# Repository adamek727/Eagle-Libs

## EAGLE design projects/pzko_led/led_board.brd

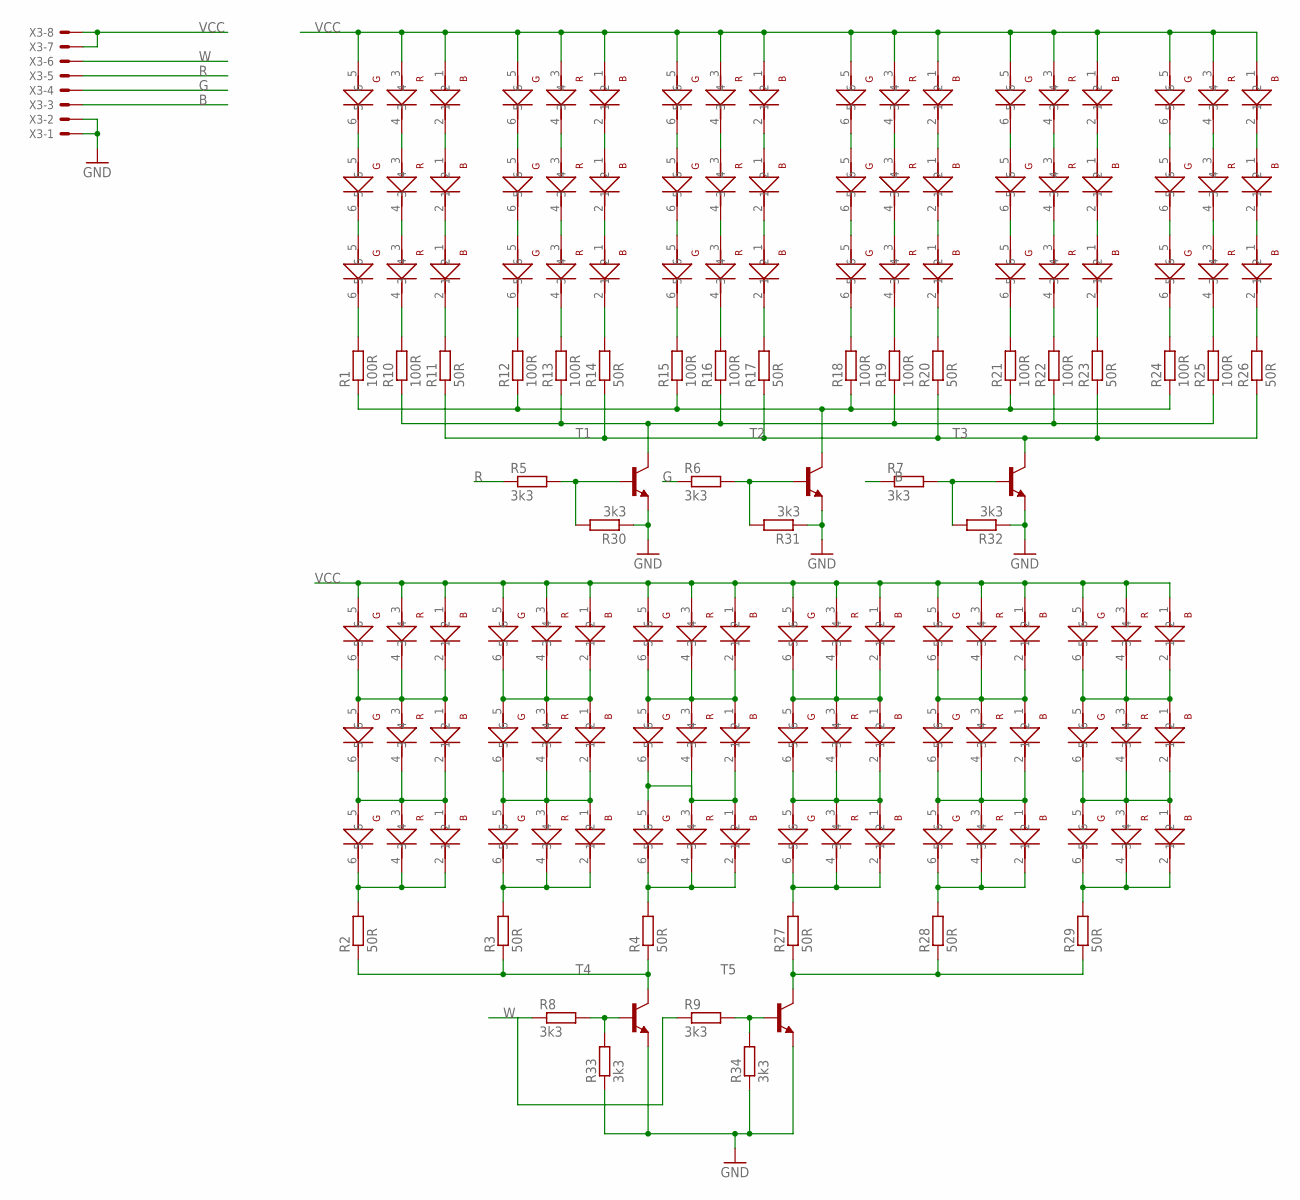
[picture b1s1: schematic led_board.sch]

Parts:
R1, R10, R12, R13, R15, R16, R18, R19, R21, R22, R24, R25: 100R; M1206
R2, R3, R4, R11, R14, R17, R20, R23, R26, R27, R28, R29: 50R; M1206
R5, R6, R7, R8, R9, R30, R31, R32, R33, R34: 3k3; M1206
T1, T2, T3, T4, T5: -NPN-SOT223; SOT223
U$1, U$2, U$3, U$4, U$5, U$6, U$7, U$8, U$9, U$10, U$11, U$12, U$13, U$14, U$15, U$16, U$17, U$18, U$19, U$20, U$21, U$22, U$23, U$24, U$25, U$26, U$27, U$28, U$29, U$30, U$31, U$32, U$33, U$34, U$35, U$38: 5050_LED
X3: KK-156-8

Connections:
B: R7.1, X3.3
G: R6.1, X3.4
GND: R30.1, R31.1, R32.1, R33.1, R34.1, T1.3 (E), T2.3 (E), T3.3 (E), T4.3 (E), T5.3 (E), X3.1, X3.2
unnamed: R6.2, R31.2, T2.1 (B)
unnamed: R7.2, R32.2, T3.1 (B)
unnamed: R11.1, R14.1, R17.1, R20.1, R23.1, R26.1, T3.4 (C)
unnamed: U$34.2, U$38.1
unnamed: R1.1, R12.1, R15.1, R18.1, R21.1, R24.1, T2.4 (C)
unnamed: U$34.4, U$38.3
unnamed: R10.1, R13.1, R16.1, R19.1, R22.1, R25.1, T1.4 (C)
unnamed: U$34.6, U$38.5
unnamed: U$1.1, U$38.2
unnamed: R5.2, R30.2, T1.1 (B)
unnamed: R8.2, R33.2, T4.1 (B)
unnamed: R9.2, R34.2, T5.1 (B)
unnamed: U$1.3, U$38.4
unnamed: U$1.5, U$38.6
unnamed: U$2.2, U$3.1
unnamed: U$2.4, U$3.3
unnamed: U$2.6, U$3.5
unnamed: U$3.2, U$4.1
unnamed: U$3.4, U$4.3
unnamed: U$3.6, U$4.5
unnamed: U$5.2, U$6.1
unnamed: U$5.4, U$6.3
unnamed: U$5.6, U$6.5
unnamed: U$6.2, U$7.1
unnamed: U$6.4, U$7.3
unnamed: U$6.6, U$7.5
unnamed: U$8.2, U$9.1
unnamed: U$8.4, U$9.3
unnamed: U$8.6, U$9.5
unnamed: U$9.2, U$10.1
unnamed: U$9.4, U$10.3
unnamed: U$9.6, U$10.5
unnamed: U$11.2, U$12.1
unnamed: U$11.4, U$12.3
unnamed: U$11.6, U$12.5
unnamed: U$12.2, U$13.1
unnamed: U$12.4, U$13.3
unnamed: U$12.6, U$13.5
unnamed: U$14.2, U$15.1
unnamed: U$14.4, U$15.3
unnamed: U$14.6, U$15.5
unnamed: U$15.2, U$16.1
unnamed: U$15.4, U$16.3
unnamed: U$15.6, U$16.5
unnamed: R1.2, U$1.6
unnamed: R10.2, U$1.4
unnamed: R11.2, U$1.2
unnamed: R12.2, U$4.6
unnamed: R13.2, U$4.4
unnamed: R15.2, U$7.6
unnamed: R16.2, U$7.4
unnamed: R17.2, U$7.2
unnamed: R18.2, U$10.6
unnamed: R19.2, U$10.4
unnamed: R21.2, U$13.6
unnamed: R22.2, U$13.4
unnamed: R23.2, U$13.2
unnamed: R24.2, U$16.6
unnamed: R26.2, U$16.2
unnamed: R25.2, U$16.4
unnamed: R20.2, U$10.2
unnamed: R14.2, U$4.2
unnamed: U$17.2, U$17.4, U$17.6, U$23.1, U$23.3, U$23.5
unnamed: U$18.2, U$18.4, U$18.6, U$24.1, U$24.3, U$24.5
unnamed: U$19.2, U$19.4, U$19.6, U$25.1, U$25.3, U$25.5
unnamed: U$20.2, U$20.4, U$20.6, U$26.1, U$26.3, U$26.5
unnamed: U$21.2, U$21.4, U$21.6, U$27.1, U$27.3, U$27.5
unnamed: U$22.2, U$22.4, U$22.6, U$28.1, U$28.3, U$28.5
unnamed: U$23.2, U$23.4, U$23.6, U$29.1, U$29.3, U$29.5
unnamed: U$24.2, U$24.4, U$24.6, U$30.1, U$30.3, U$30.5
unnamed: U$25.2, U$25.4, U$25.6, U$31.1, U$31.3, U$31.5
unnamed: U$26.2, U$26.4, U$26.6, U$32.1, U$32.3, U$32.5
unnamed: U$27.2, U$27.4, U$27.6, U$33.1, U$33.3, U$33.5
unnamed: U$28.2, U$28.4, U$28.6, U$35.1, U$35.3, U$35.5
unnamed: R2.2, U$29.2, U$29.4, U$29.6
unnamed: R29.2, U$35.2, U$35.4, U$35.6
unnamed: R28.2, U$33.2, U$33.4, U$33.6
unnamed: R27.2, U$32.2, U$32.4, U$32.6
unnamed: R4.2, U$31.2, U$31.4, U$31.6
unnamed: R3.2, U$30.2, U$30.4, U$30.6
unnamed: R27.1, R28.1, R29.1, T5.4 (C)
unnamed: R2.1, R3.1, R4.1, T4.4 (C)
R: R5.1, X3.5
VCC: U$2.1, U$2.3, U$2.5, U$5.1, U$5.3, U$5.5, U$8.1, U$8.3, U$8.5, U$11.1, U$11.3, U$11.5, U$14.1, U$14.3, U$14.5, U$17.1, U$17.3, U$17.5, U$18.1, U$18.3, U$18.5, U$19.1, U$19.3, U$19.5, U$20.1, U$20.3, U$20.5, U$21.1, U$21.3, U$21.5, U$22.1, U$22.3, U$22.5, U$34.1, U$34.3, U$34.5, X3.7, X3.8
W: R8.1, R9.1, X3.6

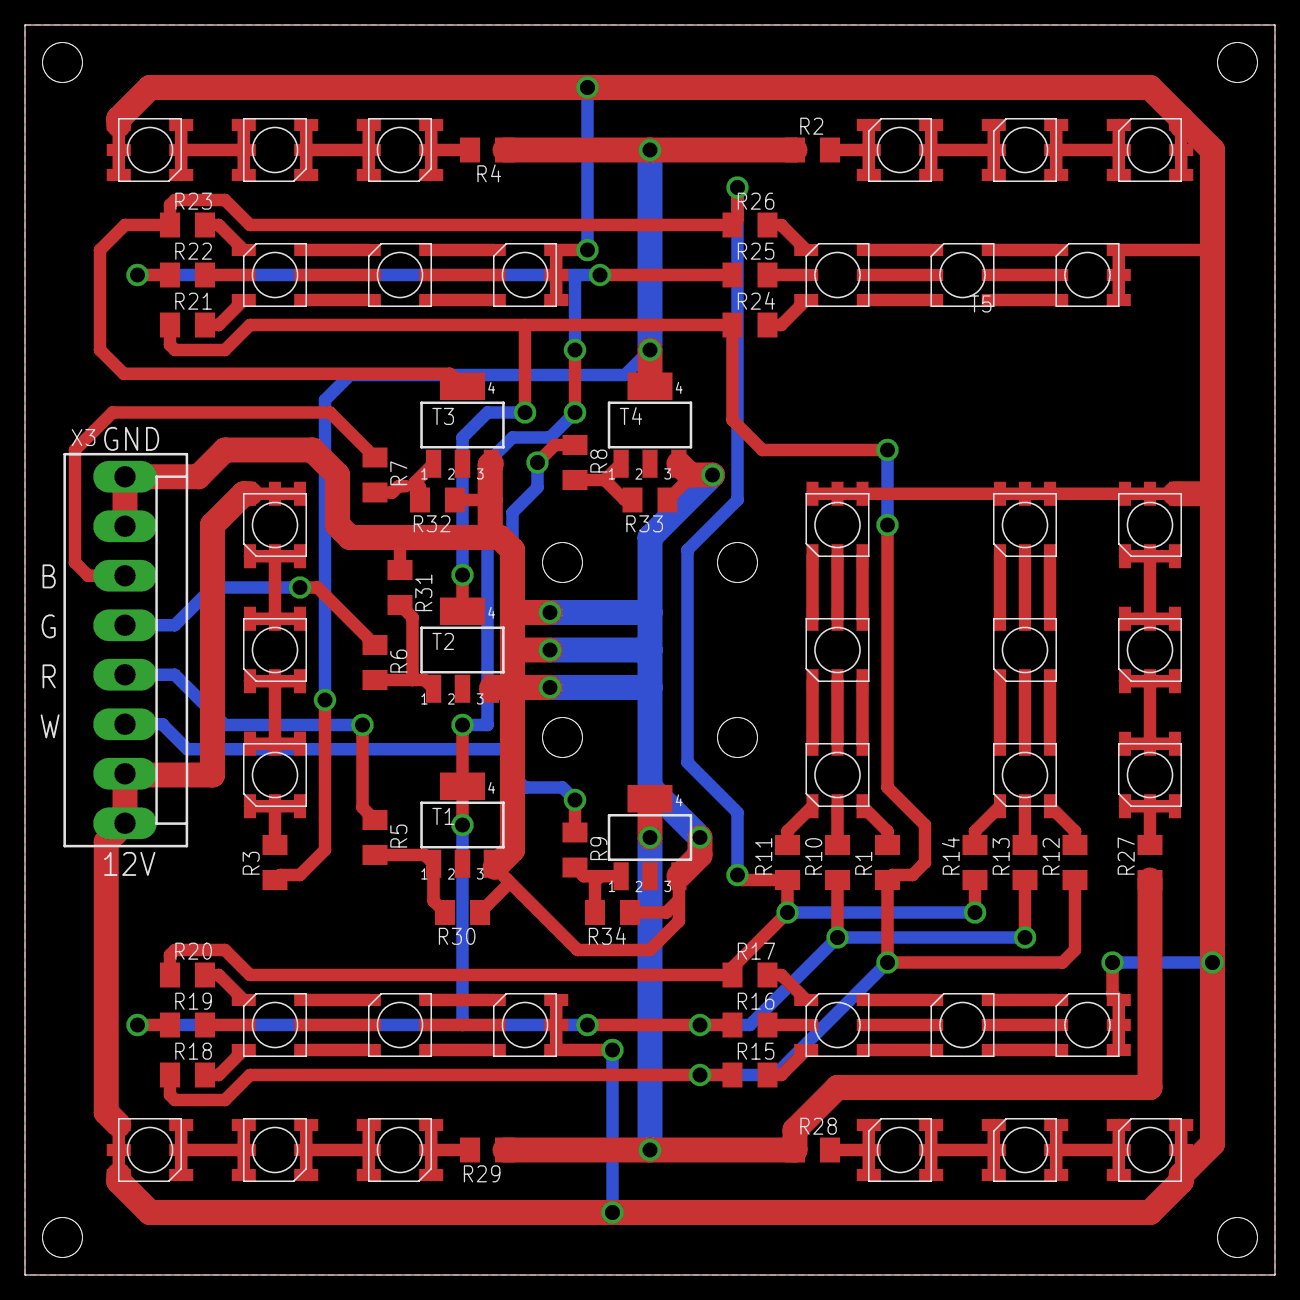
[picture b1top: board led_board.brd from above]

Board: 2 copper layers, 100.0 x 100.0 mm, 76 parts (0 on the bottom side), 88 nets.

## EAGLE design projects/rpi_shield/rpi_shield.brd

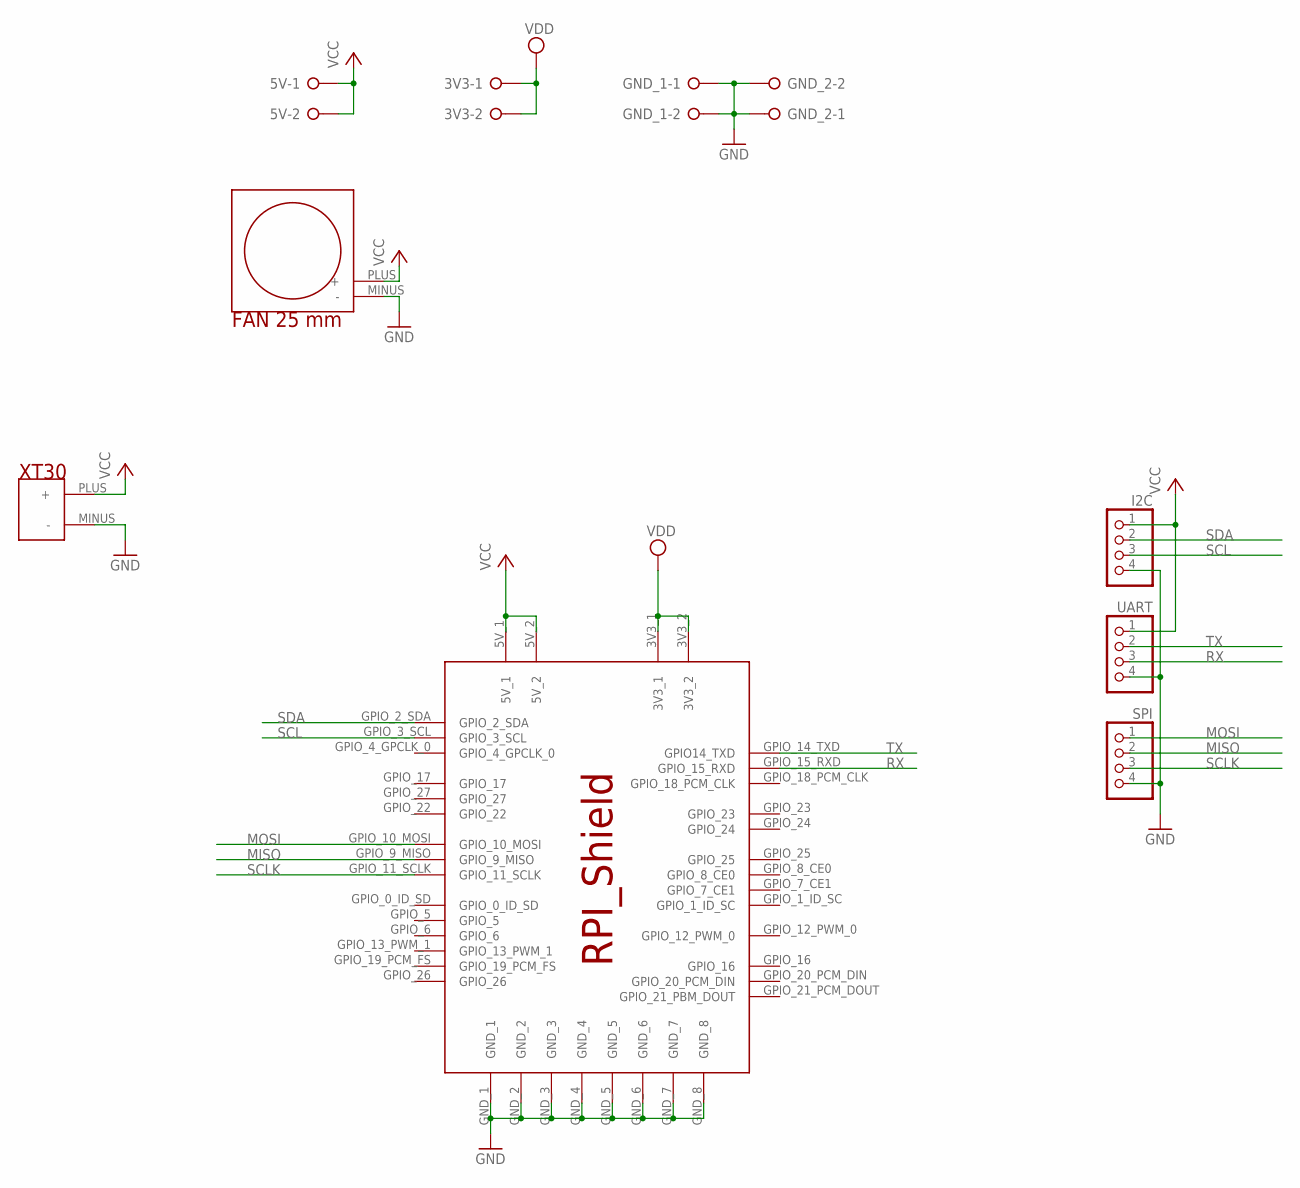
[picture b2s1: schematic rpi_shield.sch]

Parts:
3V3, 5V: W237-02P; W237-132
GND_1, GND_2: W237-02P; W237-132
I2C: PINHD-1X4/90; 1X04/90
SPI: PINHD-1X4/90; 1X04/90
U$1: RPI_SHIELD
U$2: XT30_90DEG; XT30_90DEG_FOOTPRINT
U$3: FAN_25_MM
UART: PINHD-1X4/90; 1X04/90

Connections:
GND: GND_1.1, GND_1.2, GND_2.1, GND_2.2, I2C.4, SPI.4, U$1.GND_1, U$1.GND_2, U$1.GND_3, U$1.GND_4, U$1.GND_5, U$1.GND_6, U$1.GND_7, U$1.GND_8, U$2.MINUS (-), U$3.MINUS (-), UART.4
MISO: SPI.2, U$1.GPIO_9_MISO
MOSI: SPI.1, U$1.GPIO_10_MOSI
RX: U$1.GPIO_15_RXD, UART.3
SCL: I2C.3, U$1.GPIO_3_SCL
SCLK: SPI.3, U$1.GPIO_11_SCLK
SDA: I2C.2, U$1.GPIO_2_SDA
TX: U$1.GPIO_14_TXD (GPIO14_TXD), UART.2
VCC: 5V.1, 5V.2, I2C.1, U$1.5V_1, U$1.5V_2, U$2.PLUS (+), U$3.PLUS (+), UART.1
VDD: 3V3.1, 3V3.2, U$1.3V3_1, U$1.3V3_2

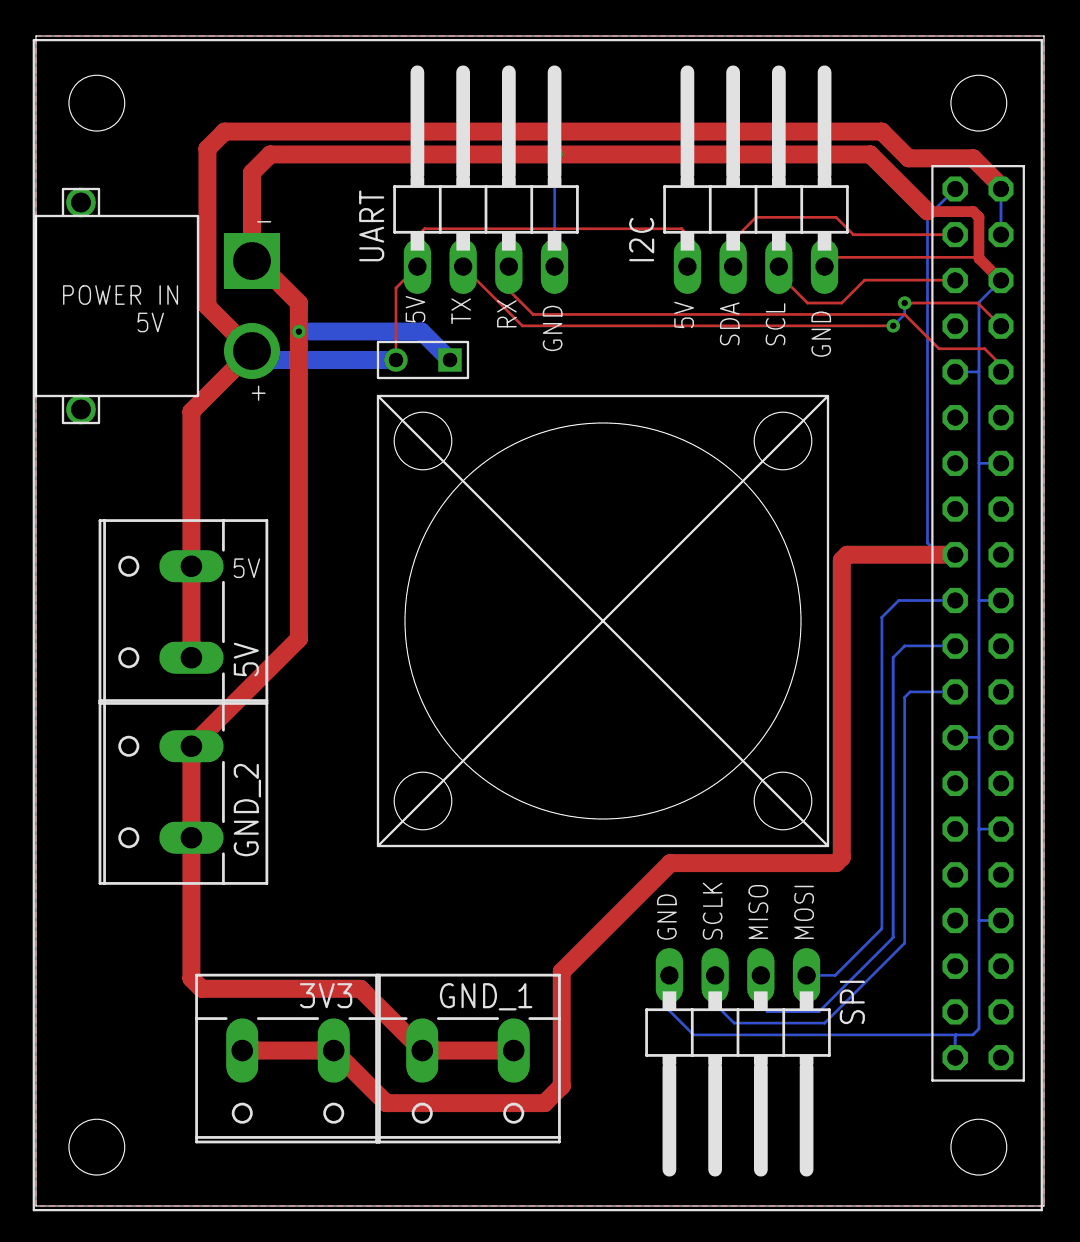
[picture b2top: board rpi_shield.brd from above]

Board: 2 copper layers, 56.0 x 65.0 mm, 10 parts (0 on the bottom side), 10 nets.

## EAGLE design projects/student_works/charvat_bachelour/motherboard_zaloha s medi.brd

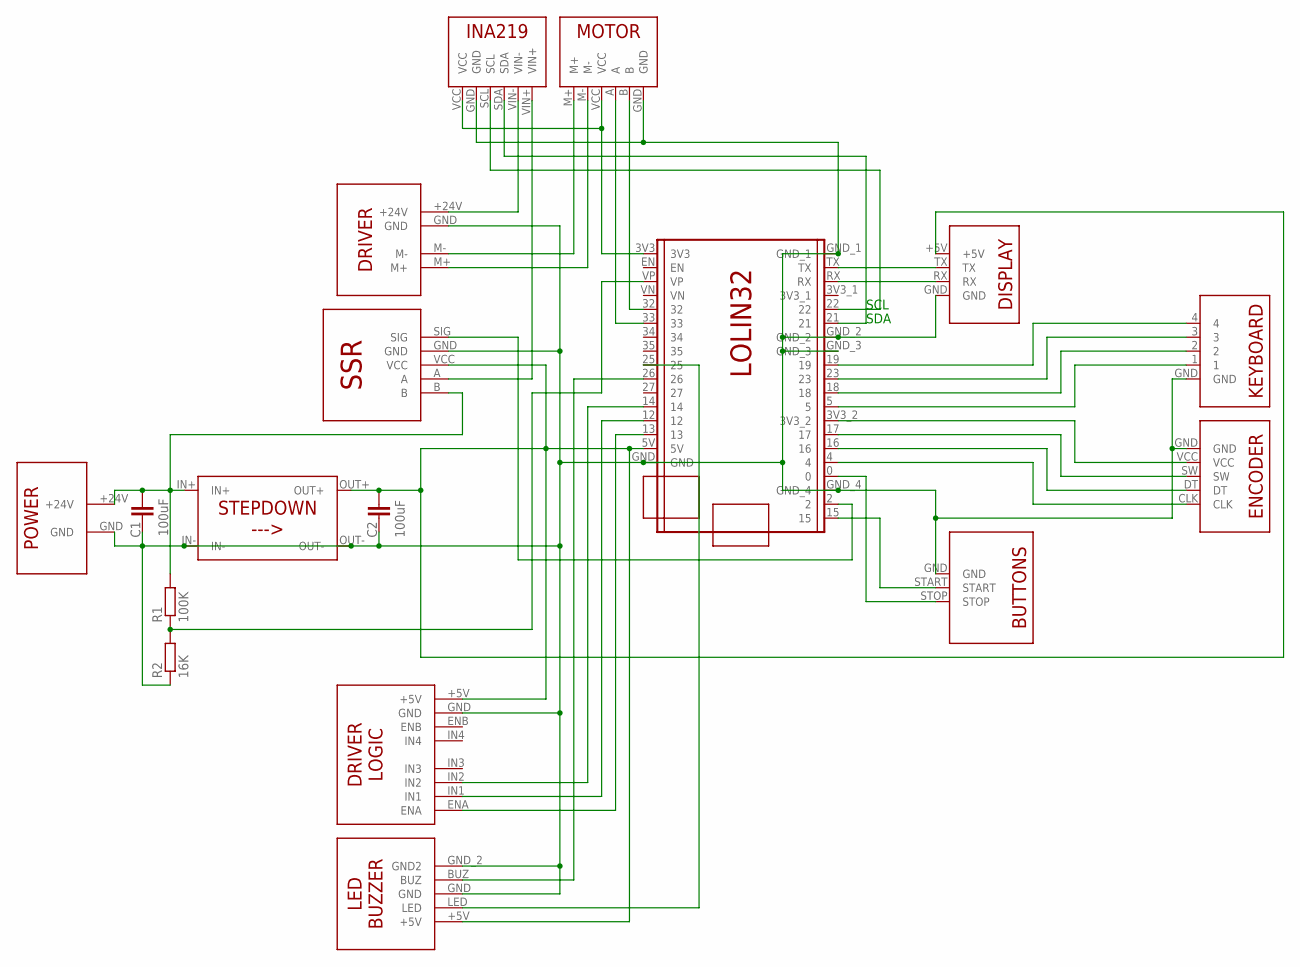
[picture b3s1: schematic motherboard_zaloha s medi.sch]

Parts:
C1, C2: 100uF; C5B2.5
R1: 100K; 0207/7
R2: 16K; 0207/7
U$1: B_DISPLAY
U$2: INA219
U$3: B_MOTOR
U$4: B_KLAVESNICE
U$5: B_LED_BUZ
U$6: B_ENCODER
U$7: B_SSR_2
U$8: B_LOLIN32
U$9: B_STEPDOWN
U$10: B_DRIVER_3
U$11: B_POWER
U$12: B_DRIVER_2
U$13: B_BUTTONS

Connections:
+5V: C2.1, U$1.+5V, U$5.+5V, U$7.VCC, U$8.5V, U$9.OUT+, U$10.+5V
GND: C1.2, C2.2, R2.1, U$1.GND, U$2.GND, U$3.GND, U$4.GND, U$5.GND, U$5.GND_2 (GND2), U$6.GND, U$7.GND, U$8.GND, U$8.GND_1, U$8.GND_2, U$8.GND_3, U$8.GND_4, U$9.IN-, U$9.OUT-, U$10.GND, U$11.GND, U$12.GND, U$13.GND
unnamed: U$6.VCC, U$8.3V3_2
unnamed: U$4.1, U$8.5
unnamed: U$3.M+, U$12.M-
unnamed: U$3.M-, U$12.M+
unnamed: U$4.2, U$8.18
unnamed: U$4.3, U$8.23
unnamed: U$6.SW, U$8.17
unnamed: U$6.DT, U$8.16
unnamed: U$4.4, U$8.19
unnamed: U$8.0, U$13.STOP
unnamed: U$7.SIG, U$8.2
unnamed: U$3.B, U$8.32
unnamed: U$1.TX, U$8.TX
unnamed: U$1.RX, U$8.RX
unnamed: U$3.A, U$8.33
unnamed: U$6.CLK, U$8.4
unnamed: U$5.BUZ, U$8.26
unnamed: U$5.LED, U$8.25
unnamed: C1.1, R1.2, U$7.B, U$9.IN+, U$11.+24V
unnamed: U$2.SDA, U$8.21
unnamed: U$8.15, U$13.START
unnamed: U$2.SCL, U$8.22
unnamed: U$2.VCC, U$3.VCC, U$8.3V3
unnamed: U$2.VIN+, U$7.A
unnamed: U$2.VIN-, U$12.+24V
unnamed: R1.1, R2.2, U$8.VP
unnamed: U$8.13, U$10.ENA
unnamed: U$8.12, U$10.IN1
unnamed: U$8.14, U$10.IN2

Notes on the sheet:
SDA
SCL

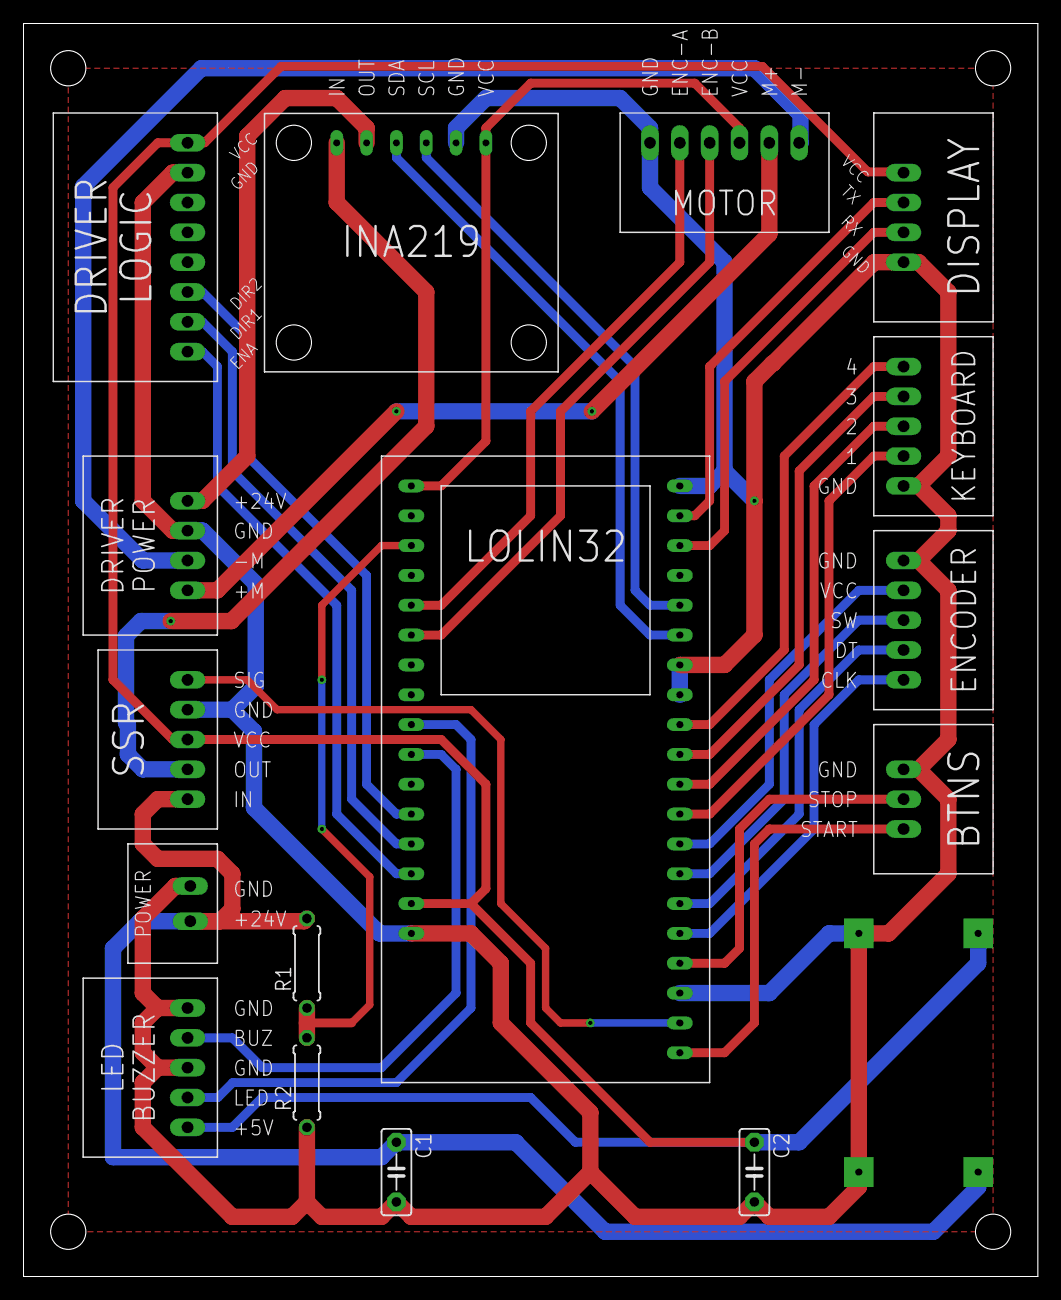
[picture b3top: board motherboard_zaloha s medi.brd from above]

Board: 2 copper layers, 86.4 x 106.7 mm, 17 parts (1 on the bottom side), 31 nets.

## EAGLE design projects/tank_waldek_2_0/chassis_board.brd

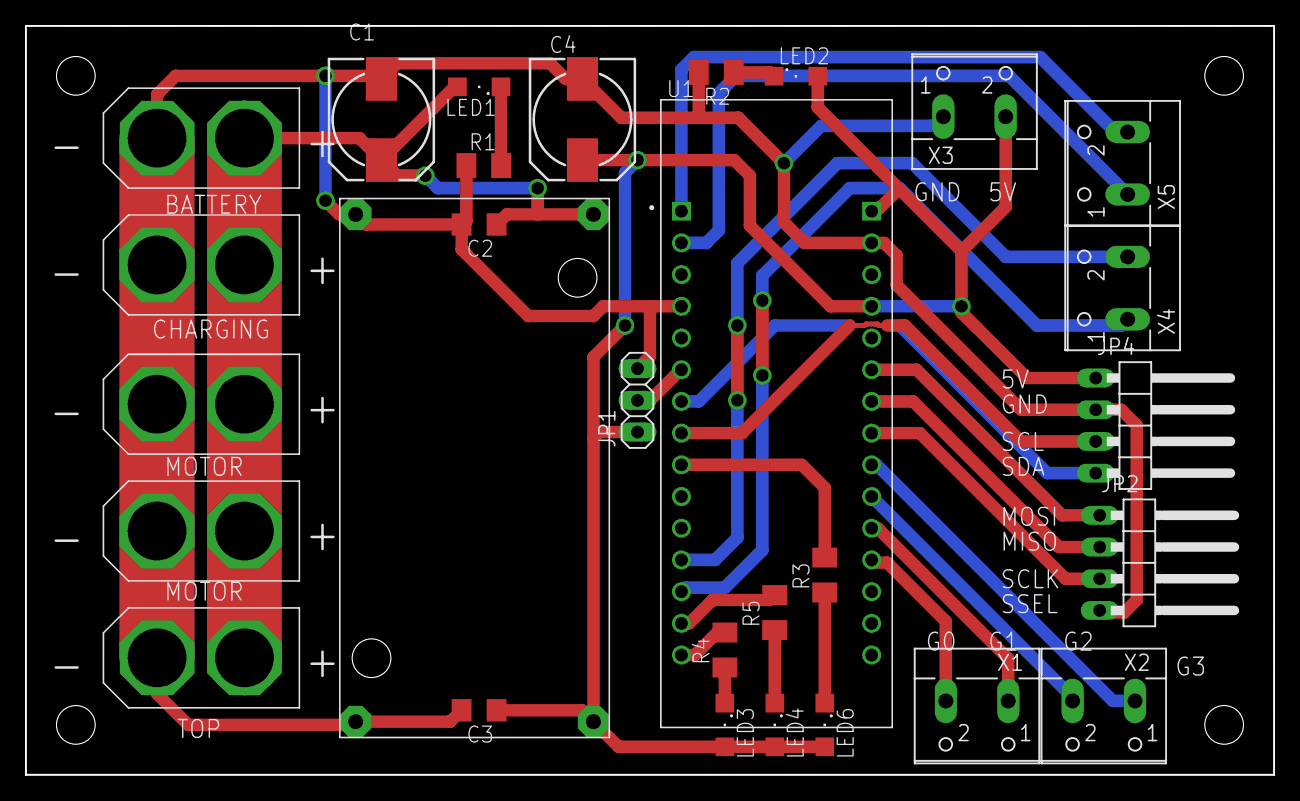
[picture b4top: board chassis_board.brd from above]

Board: 2 copper layers, 100.0 x 60.0 mm, 29 parts (0 on the bottom side), 25 nets.

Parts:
C1, C4: 140CLH-0810
C2, C3: C1206
JP1: 1X03
JP2, JP4: 1X04/90
LED1, LED2, LED3, LED4, LED6: SML1206
R1, R2, R3, R4, R5: M1206
U1: NUCLEO-L432KC; MODULE_NUCLEO-L432KC
U$1, U$2, U$3, U$4, U$5: XT60; XT60_FOOTPRINT
U$6: DC-DC-LM2596
X1, X2, X3, X4, X5: W237-102

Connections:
GND: C1.-, C2.2, C3.2, C4.-, JP1.3, JP2.4, JP4.2, R1.1, R2.2, U1.CN3_4, U1.CN4_2, U$1.MINUS, U$2.MINUS, U$3.MINUS, U$4.MINUS, U$5.MINUS, U$6.GND_IN, U$6.GND_OUT, X3.1
GPIO0: U1.CN4_12, X1.2
GPIO1: U1.CN4_11, X1.1
GPIO2: U1.CN4_10, X2.2
GPIO3: U1.CN4_9, X2.1
LED_0: R3.2, U1.CN3_9
LED_1: R4.2, U1.CN3_15
LED_2: R5.2, U1.CN3_14
MISO: JP2.2, U1.CN4_7
MOSI: JP2.1, U1.CN4_6
unnamed: C1.+, C2.1, LED1.A, U$1.PLUS, U$2.PLUS, U$3.PLUS, U$4.PLUS, U$5.PLUS, U$6.U_IN
unnamed: LED2.C, R2.1
unnamed: LED6.C, R3.1
unnamed: LED1.C, R1.2
unnamed: LED3.C, R4.1
unnamed: LED4.C, R5.1
PWM_LEFT_B: U1.CN3_2, X5.1
PWM_LEFT_F: U1.CN3_1, X5.2
PWM_RIGHT_B: U1.CN3_13, X4.1
PWM_RIGHT_F: U1.CN3_12, X4.2
SCL: JP4.3, U1.CN3_8
SCLK: JP2.3, U1.CN4_8
SDA: JP4.4, U1.CN3_7
SSEL: JP1.2, U1.CN3_6
VCC: C3.1, C4.+, JP1.1, JP4.1, LED2.A, LED3.A, LED4.A, LED6.A, U1.CN4_1, U1.CN4_4, U$6.U_OUT, X3.2

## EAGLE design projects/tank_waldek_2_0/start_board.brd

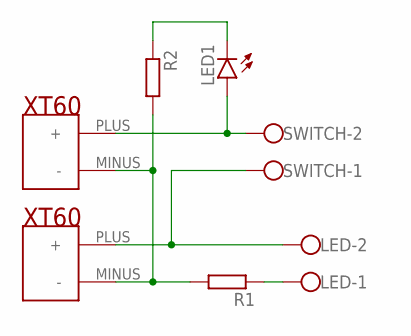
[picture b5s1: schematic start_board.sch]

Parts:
LED: W237-102
LED1: LEDCHIPLED_1206; CHIPLED_1206
R1, R2: R-EU_M1206; M1206
SWITCH: W237-102
U$1, U$2: XT60; XT60_FOOTPRINT

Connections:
unnamed: R1.2, R2.2, U$1.MINUS (-), U$2.MINUS (-)
unnamed: LED1.A, SWITCH.2, U$1.PLUS (+)
unnamed: LED.2, SWITCH.1, U$2.PLUS (+)
unnamed: LED1.C, R2.1
unnamed: LED.1, R1.1

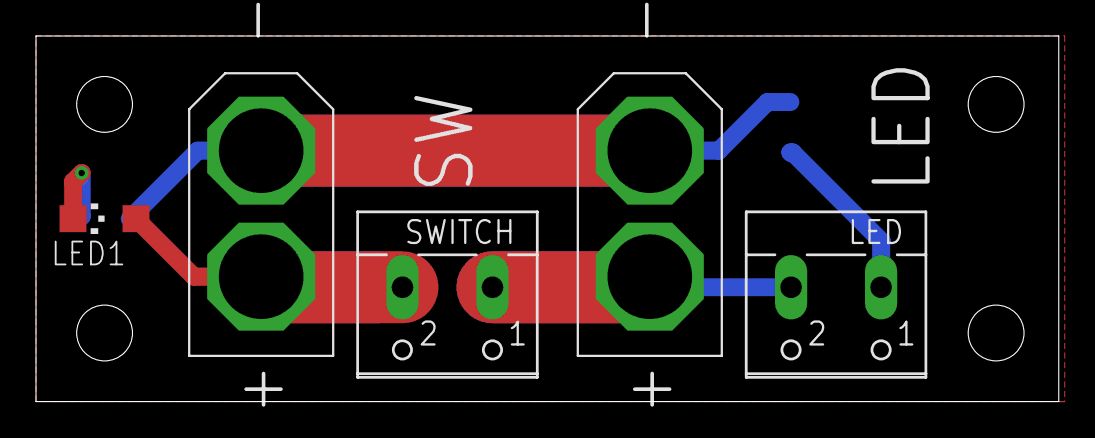
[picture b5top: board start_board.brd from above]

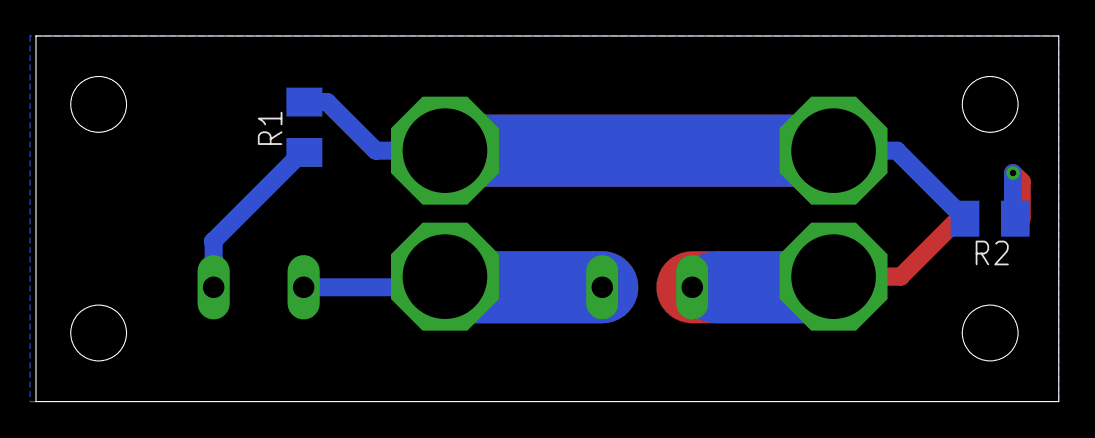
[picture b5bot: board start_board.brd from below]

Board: 2 copper layers, 56.8 x 20.3 mm, 7 parts (2 on the bottom side), 5 nets.

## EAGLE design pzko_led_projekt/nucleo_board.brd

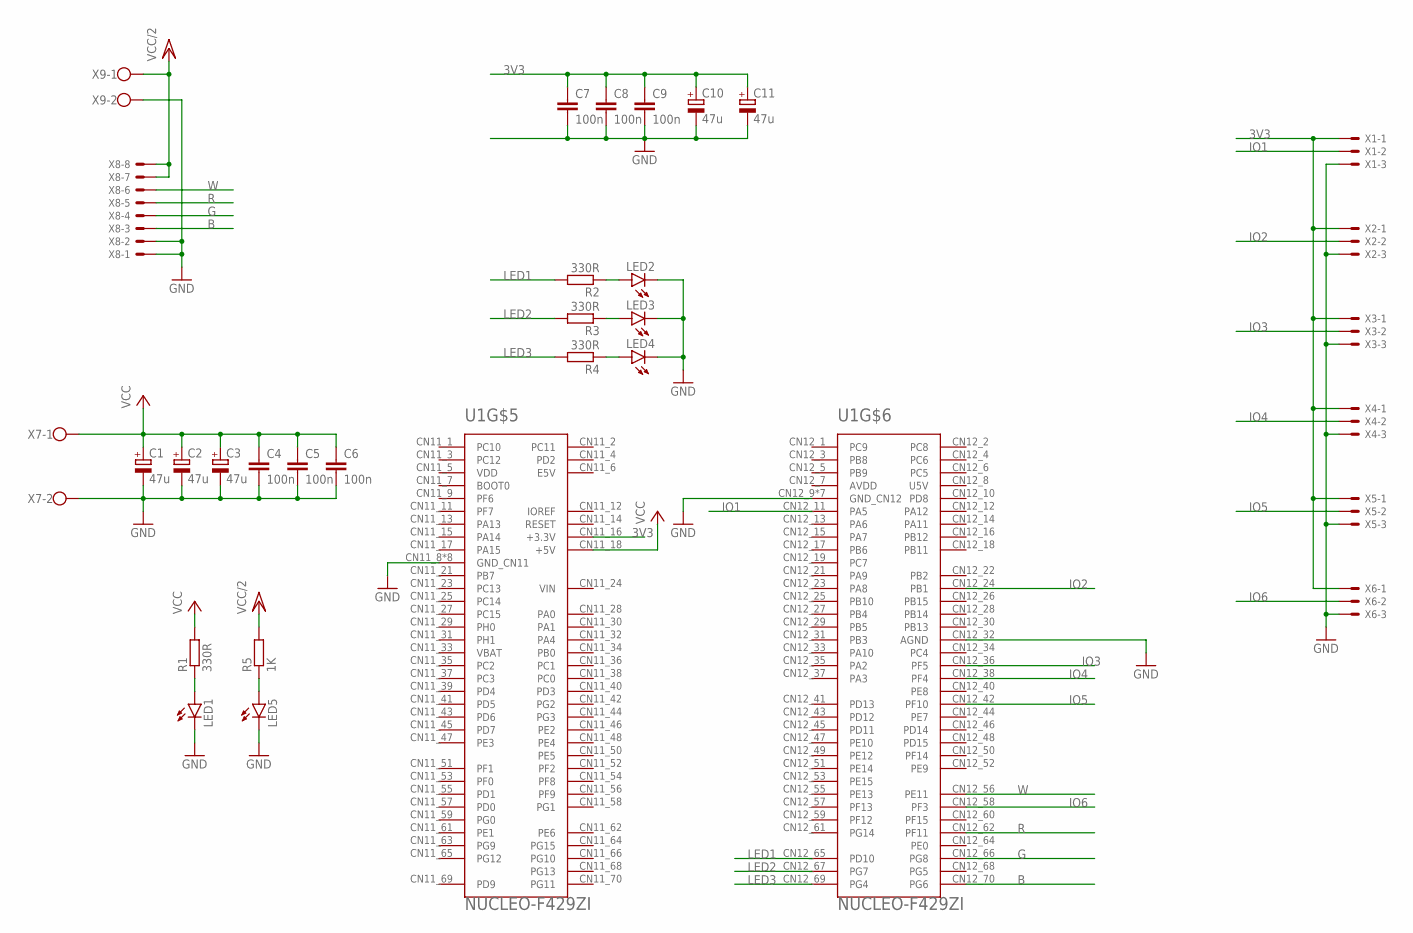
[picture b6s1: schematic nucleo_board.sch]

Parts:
C1, C2, C3, C10, C11: 47u; 153CLV-1010
C4, C5, C6, C7, C8, C9: 100n; C1206
LED1, LED2, LED3, LED4, LED5: LEDCHIPLED_1206; CHIPLED_1206
R1, R2, R3, R4: 330R; M1206
R5: 1K; M1206
U1: NUCLEO-F429ZI; MODULE_NUCLEO-F429ZI
X1, X2, X3, X4, X5, X6: KK-156-3
X7, X9: W237-102
X8: KK-156-8

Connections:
3V3: C7.1, C8.1, C9.1, C10.+, C11.+, U1.CN11_16 (+3.3V), X1.1, X2.1, X3.1, X4.1, X5.1, X6.1
B: U1.CN12_70 (PG6), X8.3
G: U1.CN12_66 (PG8), X8.4
GND: C1.-, C2.-, C3.-, C4.2, C5.2, C6.2, C7.2, C8.2, C9.2, C10.-, C11.-, LED1.C, LED2.C, LED3.C, LED4.C, LED5.C, U1.CN11_8 (GND_CN11), U1.CN11_19 (GND_CN11), U1.CN11_20 (GND_CN11), U1.CN11_22 (GND_CN11), U1.CN11_49 (GND_CN11), U1.CN11_60 (GND_CN11), U1.CN11_71 (GND_CN11), U1.CN11_72 (GND_CN11), U1.CN12_9 (GND_CN12), U1.CN12_20 (GND_CN12), U1.CN12_32 (AGND), U1.CN12_39 (GND_CN12), U1.CN12_54 (GND_CN12), U1.CN12_63 (GND_CN12), U1.CN12_71 (GND_CN12), U1.CN12_72 (GND_CN12), X1.3, X2.3, X3.3, X4.3, X5.3, X6.3, X7.2, X8.1, X8.2, X9.2
IO1: U1.CN12_11 (PA5), X1.2
IO2: U1.CN12_24 (PB1), X2.2
IO3: U1.CN12_36 (PF5), X3.2
IO4: U1.CN12_38 (PF4), X4.2
IO5: U1.CN12_42 (PF10), X5.2
IO6: U1.CN12_58 (PF3), X6.2
LED1: R2.2, U1.CN12_65 (PD10)
LED2: R3.2, U1.CN12_67 (PG7)
LED3: R4.2, U1.CN12_69 (PG4)
unnamed: LED1.A, R1.1
unnamed: LED5.A, R5.1
unnamed: LED3.A, R3.1
unnamed: LED4.A, R4.1
unnamed: LED2.A, R2.1
R: U1.CN12_62 (PF11), X8.5
VCC: C1.+, C2.+, C3.+, C4.1, C5.1, C6.1, R1.2, U1.CN11_18 (+5V), X7.1
VCC/2: R5.2, X8.7, X8.8, X9.1
W: U1.CN12_56 (PE11), X8.6

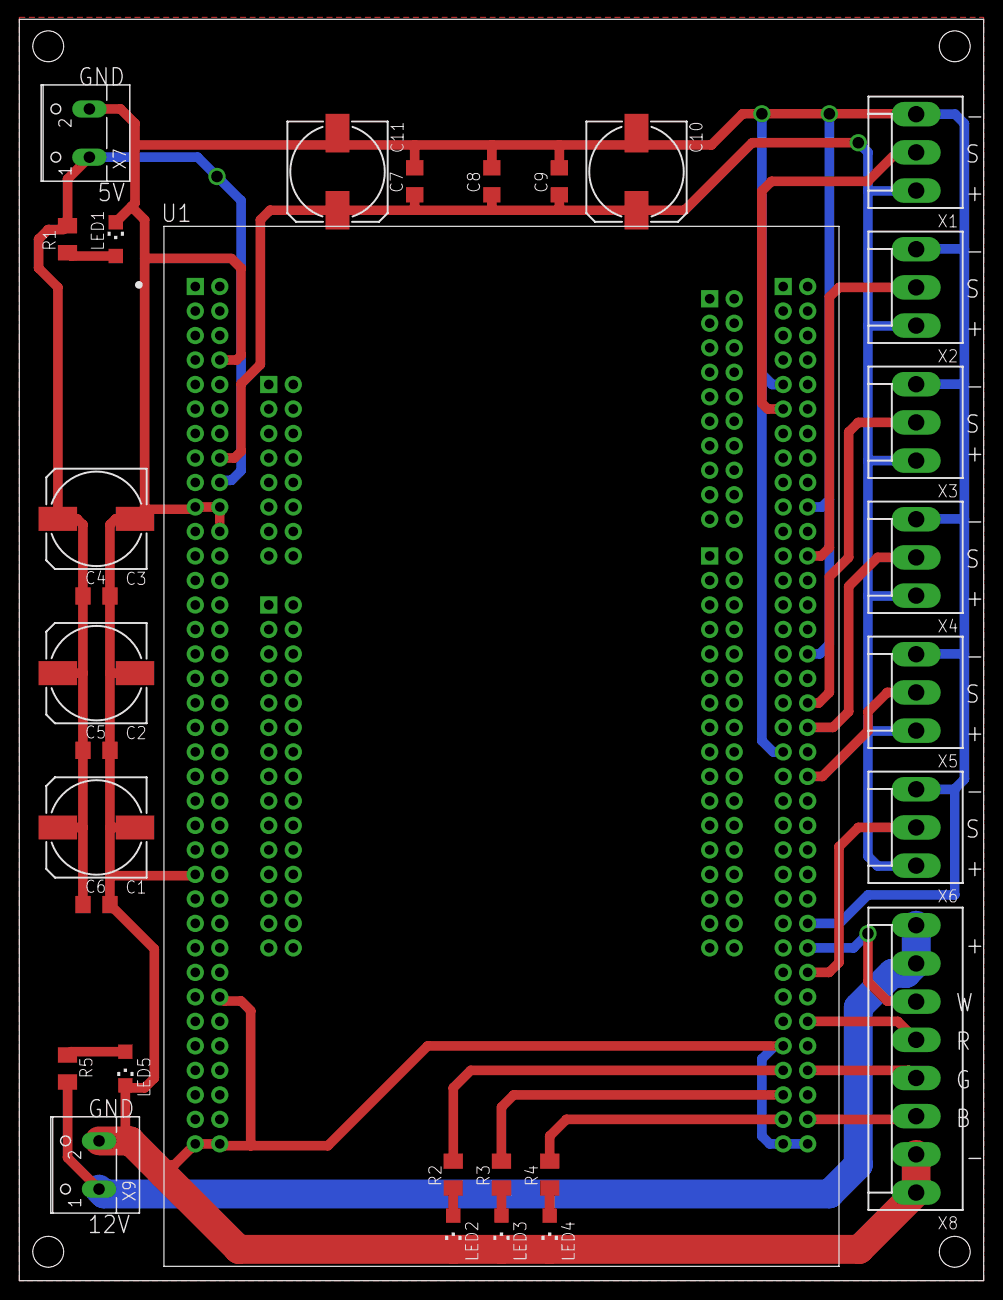
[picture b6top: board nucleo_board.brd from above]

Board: 2 copper layers, 100.0 x 130.8 mm, 31 parts (0 on the bottom side), 22 nets.
